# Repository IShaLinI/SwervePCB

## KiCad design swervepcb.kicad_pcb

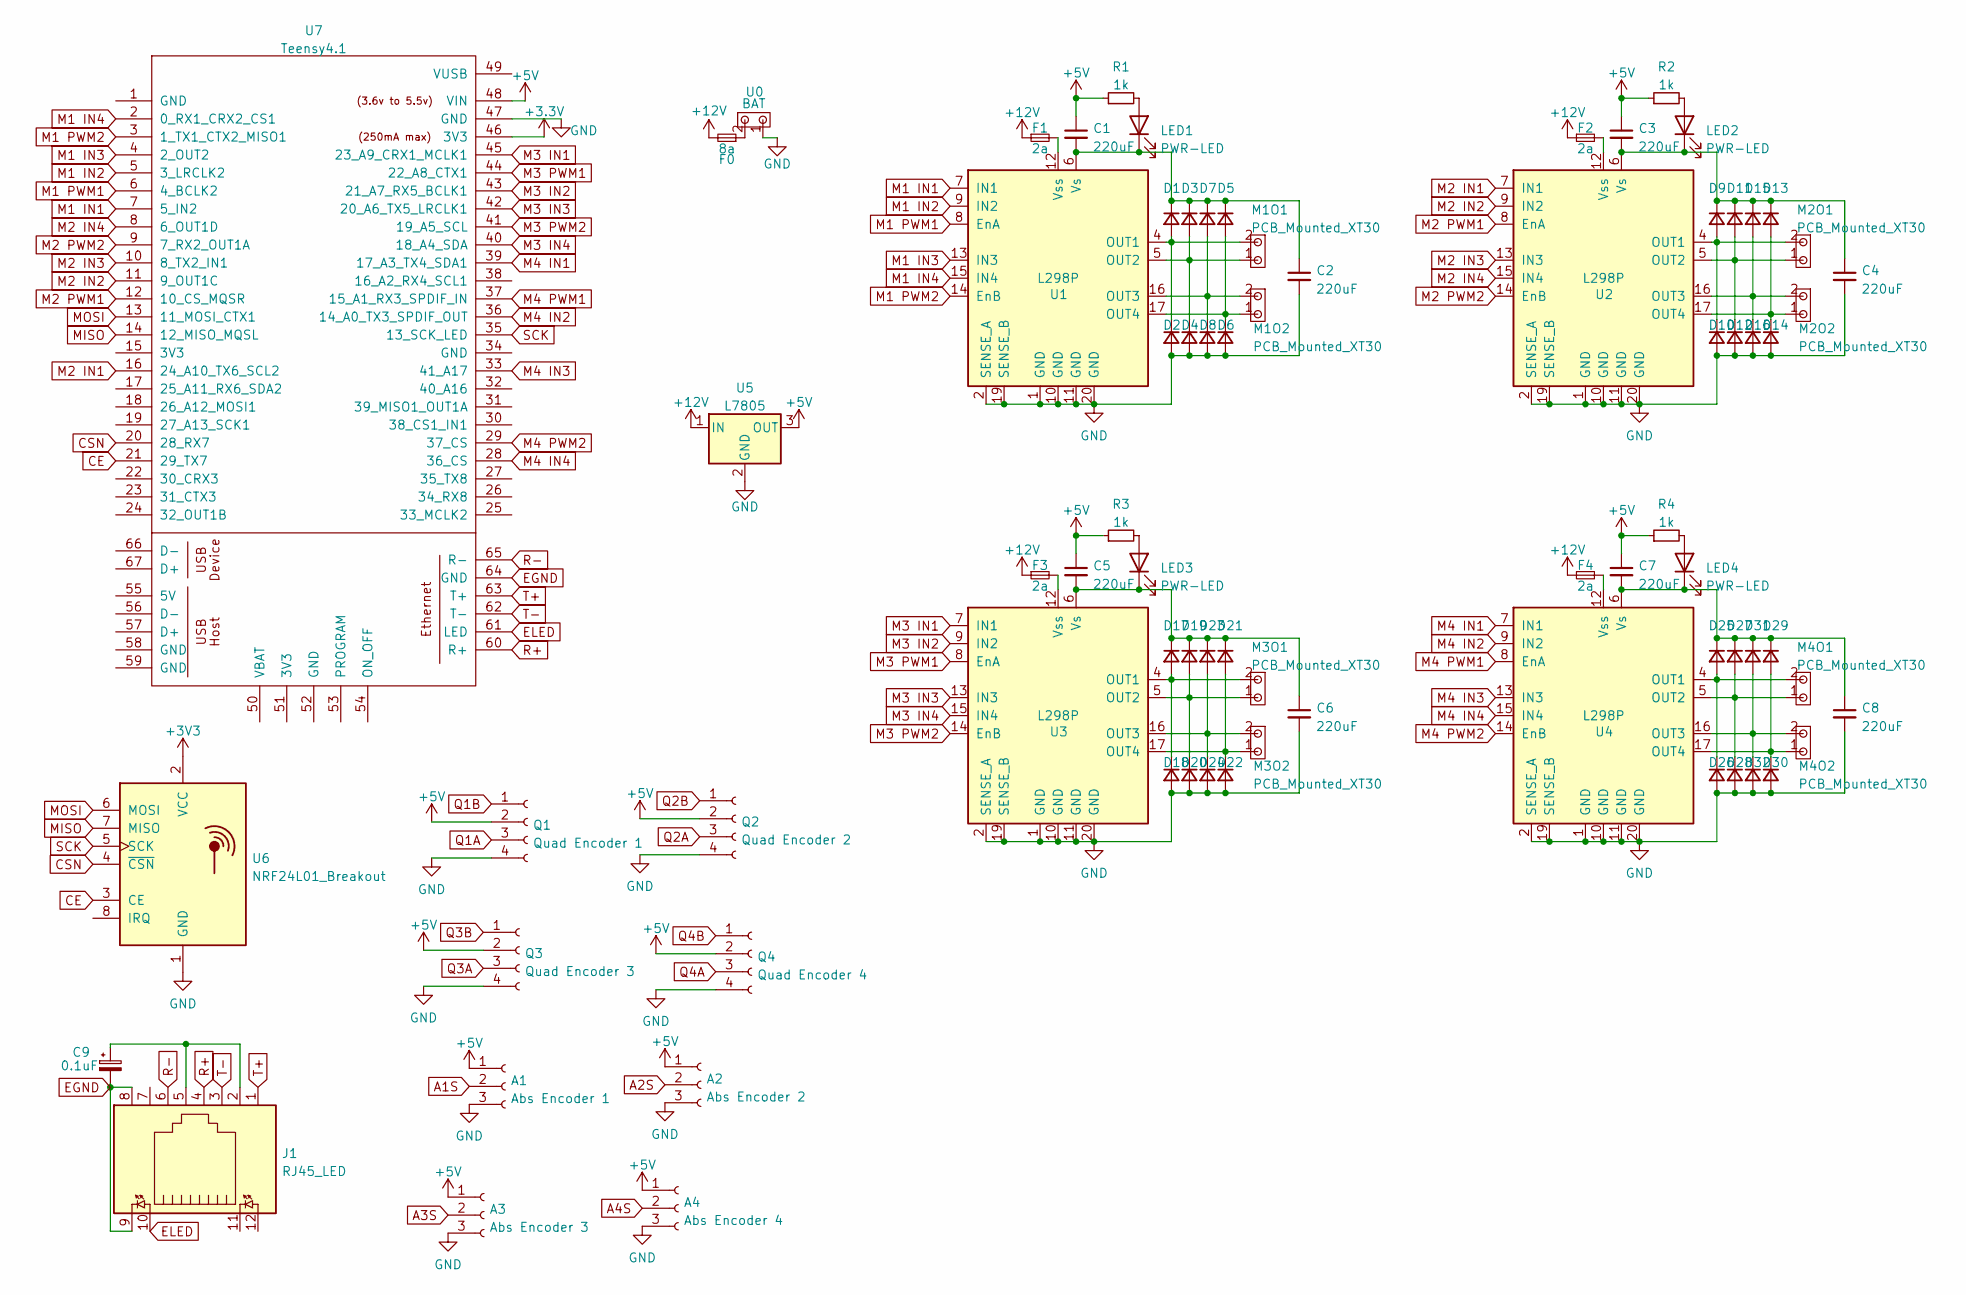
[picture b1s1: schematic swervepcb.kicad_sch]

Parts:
A1: Abs Encoder 1; PinHeader_1x03_P1.00mm_Vertical
A2: Abs Encoder 2; PinHeader_1x03_P1.00mm_Vertical
A3: Abs Encoder 3; PinHeader_1x03_P1.00mm_Vertical
A4: Abs Encoder 4; PinHeader_1x03_P1.00mm_Vertical
C1, C2, C3, C4, C5, C6, C7, C8: 220uF; CP_Radial_D8.0mm_P3.50mm
C9: 0.1uF; D_DO-41_SOD81_P7.62mm_Horizontal
D1, D2, D3, D4, D5, D6, D7, D8, D9, D10, D11, D12, D13, D14, D15, D16, D17, D18, D19, D20, D21, D22, D23, D24, D25, D26, D27, D28, D29, D30, D31, D32: D_DO-41_SOD81_P7.62mm_Horizontal
F0: 8a; Fuseholder_Cylinder-5x20mm_Schurter_0031_8201_Horizontal_Op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
F1, F2, F3, F4: 2a; Fuseholder_Cylinder-5x20mm_Schurter_0031_8201_Horizontal_Op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
J1: RJ45_LED; RJ45_Cetus_J1B1211CCD_Horizontal
LED1, LED2, LED3, LED4: PWR-LED; LED_D5.0mm
M1O1, M1O2, M2O1, M2O2, M3O1, M3O2, M4O1, M4O2: PCB_Mounted_XT30; RightAngleXT30-M
Q1: Quad Encoder 1; PinHeader_1x04_P1.00mm_Vertical
Q2: Quad Encoder 2; PinHeader_1x04_P1.00mm_Vertical
Q3: Quad Encoder 3; PinHeader_1x04_P1.00mm_Vertical
Q4: Quad Encoder 4; PinHeader_1x04_P1.00mm_Vertical
R1, R2, R3, R4: 1k; R_Axial_DIN0309_L9.0mm_D3.2mm_P12.70mm_Horizontal
U0: BAT; RightAngleXT30-F
U1, U2, U3, U4: L298P
U5: L7805; STMicroelectronics-TO-220-3-0-0-0
U6: NRF24L01_Breakout; nRF24L01_Breakout
U7: Teensy4.1; Teensy41

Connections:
+3.3V: U7.46 (3V3)
+3V3: U6.2 (VCC)
+5V: A1.1, A2.1, A3.1, A4.1, C1.1, C3.1, C5.1, C7.1, Q1.2, Q2.2, Q3.2, Q4.2, R1.1, R2.1, R3.1, R4.1, U5.3 (OUT), U7.48 (VIN)
+12V: F0.2, F1.1, F2.1, F3.1, F4.1, U5.1 (IN)
A1S: A1.2
A2S: A2.2
A3S: A3.2
A4S: A4.2
CE: U6.3 (CE), U7.21 (29_TX7)
CSN: U6.4 (~CSN), U7.20 (28_RX7)
EGND: C9.2, J1.8, J1.9, U7.64 (GND)
ELED: J1.10, U7.61 (LED)
GND: A1.3, A2.3, A3.3, A4.3, C2.2, C4.2, C6.2, C8.2, D2.2 (A), D4.2 (A), D6.2 (A), D8.2 (A), D10.2 (A), D12.2 (A), D14.2 (A), D16.2 (A), D18.2 (A), D20.2 (A), D22.2 (A), D24.2 (A), D26.2 (A), D28.2 (A), D30.2 (A), D32.2 (A), Q1.4, Q2.4, Q3.4, Q4.4, U0.1, U1.1 (GND), U1.2 (SENSE_A), U1.10 (GND), U1.11 (GND), U1.19 (SENSE_B), U1.20 (GND), U2.1 (GND), U2.2 (SENSE_A), U2.10 (GND), U2.11 (GND), U2.19 (SENSE_B), U2.20 (GND), U3.1 (GND), U3.2 (SENSE_A), U3.10 (GND), U3.11 (GND), U3.19 (SENSE_B), U3.20 (GND), U4.1 (GND), U4.2 (SENSE_A), U4.10 (GND), U4.11 (GND), U4.19 (SENSE_B), U4.20 (GND), U5.2 (GND), U6.1 (GND), U7.47 (GND)
M1 IN1: U1.7 (IN1), U7.7 (5_IN2)
M1 IN2: U1.9 (IN2), U7.5 (3_LRCLK2)
M1 IN3: U1.13 (IN3), U7.4 (2_OUT2)
M1 IN4: U1.15 (IN4), U7.2 (0_RX1_CRX2_CS1)
M1 PWM1: U1.8 (EnA), U7.6 (4_BCLK2)
M1 PWM2: U1.14 (EnB), U7.3 (1_TX1_CTX2_MISO1)
M2 IN1: U2.7 (IN1), U7.16 (24_A10_TX6_SCL2)
M2 IN2: U2.9 (IN2), U7.11 (9_OUT1C)
M2 IN3: U2.13 (IN3), U7.10 (8_TX2_IN1)
M2 IN4: U2.15 (IN4), U7.8 (6_OUT1D)
M2 PWM1: U2.8 (EnA), U7.12 (10_CS_MQSR)
M2 PWM2: U2.14 (EnB), U7.9 (7_RX2_OUT1A)
M3 IN1: U3.7 (IN1), U7.45 (23_A9_CRX1_MCLK1)
M3 IN2: U3.9 (IN2), U7.43 (21_A7_RX5_BCLK1)
M3 IN3: U3.13 (IN3), U7.42 (20_A6_TX5_LRCLK1)
M3 IN4: U3.15 (IN4), U7.40 (18_A4_SDA)
M3 PWM1: U3.8 (EnA), U7.44 (22_A8_CTX1)
M3 PWM2: U3.14 (EnB), U7.41 (19_A5_SCL)
M4 IN1: U4.7 (IN1), U7.39 (17_A3_TX4_SDA1)
M4 IN2: U4.9 (IN2), U7.36 (14_A0_TX3_SPDIF_OUT)
M4 IN3: U4.13 (IN3), U7.33 (41_A17)
M4 IN4: U4.15 (IN4), U7.28 (36_CS)
M4 PWM1: U4.8 (EnA), U7.37 (15_A1_RX3_SPDIF_IN)
M4 PWM2: U4.14 (EnB), U7.29 (37_CS)
MISO: U6.7 (MISO), U7.14 (12_MISO_MQSL)
MOSI: U6.6 (MOSI), U7.13 (11_MOSI_CTX1)
unnamed: C1.2, C2.1, D1.1 (K), D3.1 (K), D5.1 (K), D7.1 (K), LED1.1 (K), U1.6 (Vs)
unnamed: C3.2, C4.1, D9.1 (K), D11.1 (K), D13.1 (K), D15.1 (K), LED2.1 (K), U2.6 (Vs)
unnamed: C5.2, C6.1, D17.1 (K), D19.1 (K), D21.1 (K), D23.1 (K), LED3.1 (K), U3.6 (Vs)
unnamed: C7.2, C8.1, D25.1 (K), D27.1 (K), D29.1 (K), D31.1 (K), LED4.1 (K), U4.6 (Vs)
unnamed: C9.1, J1.2, J1.5
unnamed: D1.2 (A), D2.1 (K), M1O1.2, U1.4 (OUT1)
unnamed: D3.2 (A), D4.1 (K), M1O1.1, U1.5 (OUT2)
unnamed: D5.2 (A), D6.1 (K), M1O2.1, U1.17 (OUT4)
unnamed: D7.2 (A), D8.1 (K), M1O2.2, U1.16 (OUT3)
unnamed: D9.2 (A), D10.1 (K), M2O1.2, U2.4 (OUT1)
unnamed: D11.2 (A), D12.1 (K), M2O1.1, U2.5 (OUT2)
unnamed: D13.2 (A), D14.1 (K), M2O2.1, U2.17 (OUT4)
unnamed: D15.2 (A), D16.1 (K), M2O2.2, U2.16 (OUT3)
unnamed: D17.2 (A), D18.1 (K), M3O1.2, U3.4 (OUT1)
unnamed: D19.2 (A), D20.1 (K), M3O1.1, U3.5 (OUT2)
unnamed: D21.2 (A), D22.1 (K), M3O2.1, U3.17 (OUT4)
unnamed: D23.2 (A), D24.1 (K), M3O2.2, U3.16 (OUT3)
unnamed: D25.2 (A), D26.1 (K), M4O1.2, U4.4 (OUT1)
unnamed: D27.2 (A), D28.1 (K), M4O1.1, U4.5 (OUT2)
unnamed: D29.2 (A), D30.1 (K), M4O2.1, U4.17 (OUT4)
unnamed: D31.2 (A), D32.1 (K), M4O2.2, U4.16 (OUT3)
unnamed: F0.1, U0.2
unnamed: F1.2, U1.12 (Vss)
unnamed: F2.2, U2.12 (Vss)
unnamed: F3.2, U3.12 (Vss)
unnamed: F4.2, U4.12 (Vss)
unnamed: LED1.2 (A), R1.2
unnamed: LED2.2 (A), R2.2
unnamed: LED3.2 (A), R3.2
unnamed: LED4.2 (A), R4.2
Q1A: Q1.3
Q1B: Q1.1
Q2A: Q2.3
Q2B: Q2.1
Q3A: Q3.3
Q3B: Q3.1
Q4A: Q4.3
Q4B: Q4.1
R+: J1.4, U7.60 (R+)
R-: J1.6, U7.65 (R-)
SCK: U6.5 (SCK), U7.35 (13_SCK_LED)
T+: J1.1, U7.63 (T+)
T-: J1.3, U7.62 (T-)

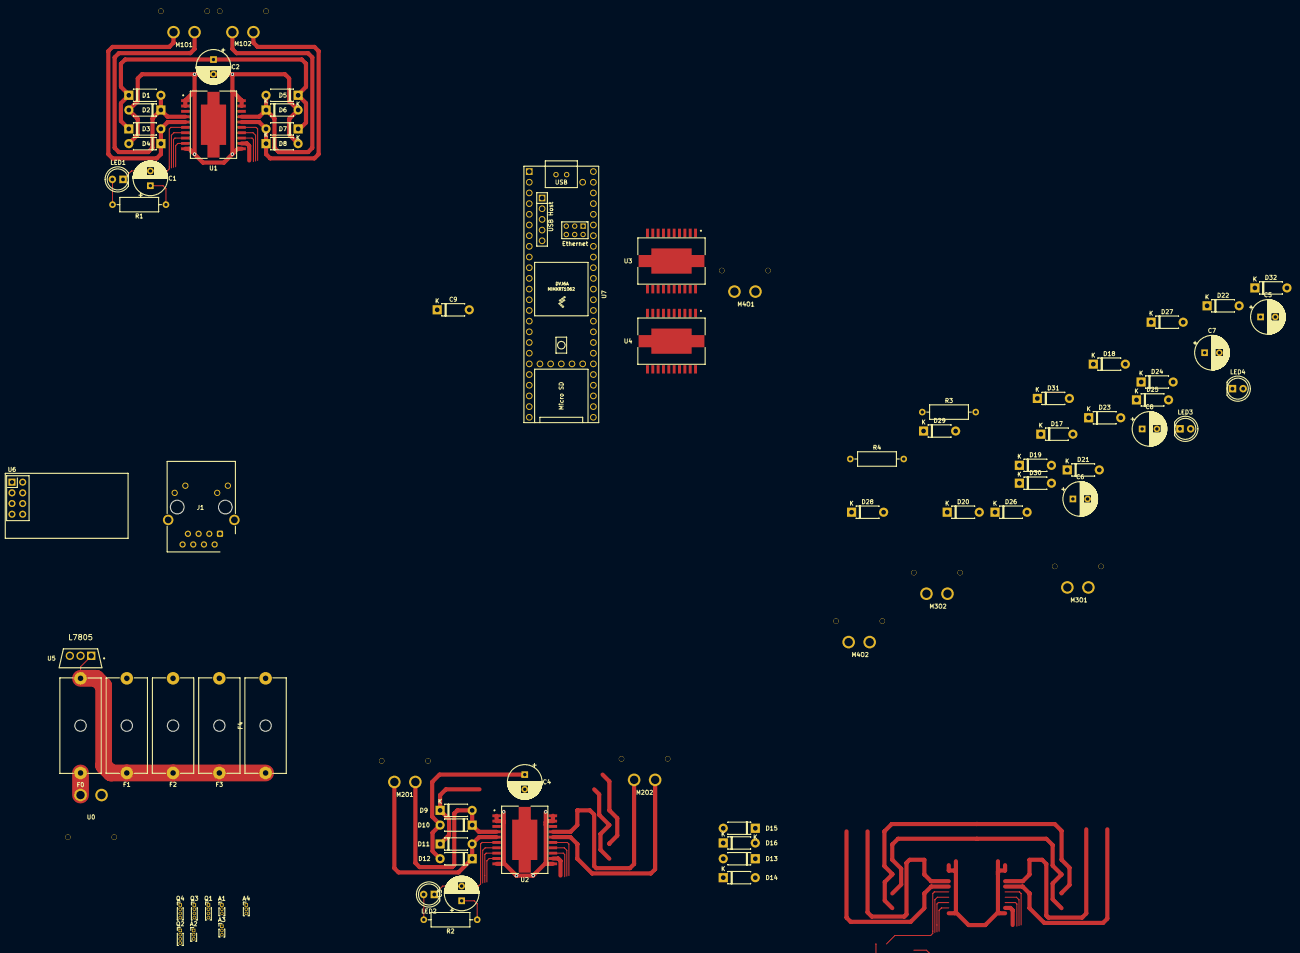
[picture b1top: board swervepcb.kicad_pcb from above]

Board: 2 copper layers, 79 parts (0 on the bottom side), 68 nets.

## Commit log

2022-11-09 init
2022-11-11 progress
2022-11-11 finalized motor controller design
2022-11-12 encoder pins
